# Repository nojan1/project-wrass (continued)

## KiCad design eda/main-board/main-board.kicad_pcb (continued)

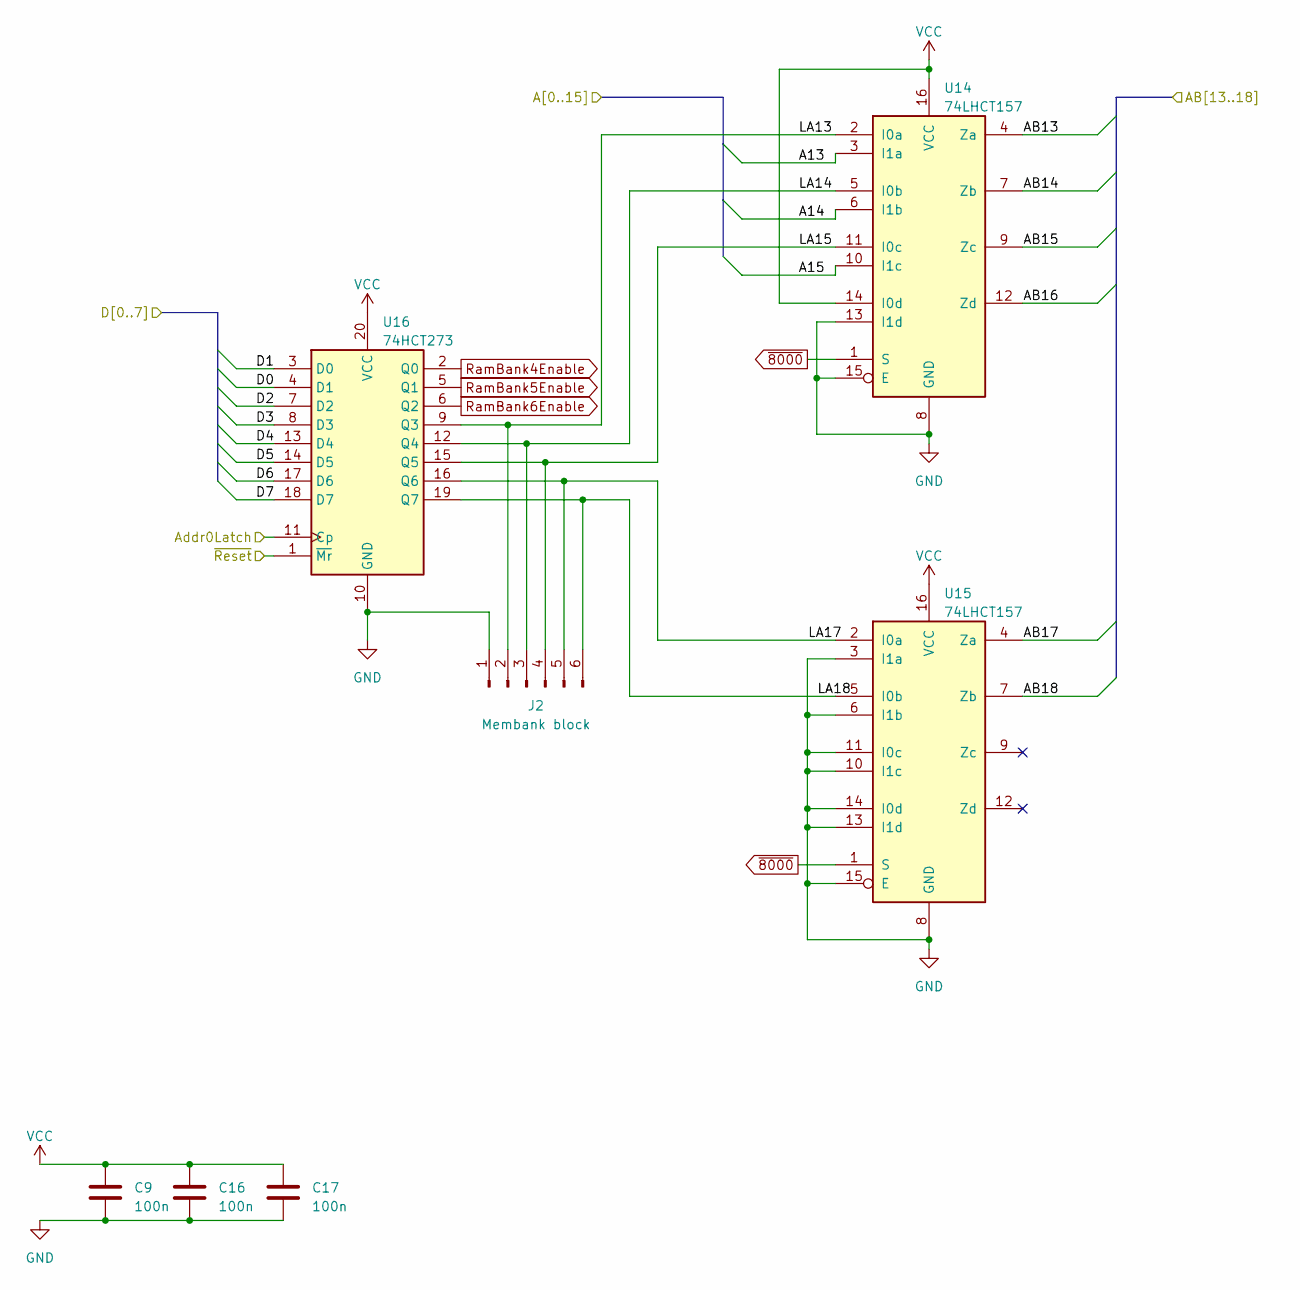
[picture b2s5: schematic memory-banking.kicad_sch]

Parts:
C9, C16, C17: 100n; C_Disc_D3.8mm_W2.6mm_P2.50mm
J2: Membank block; PinHeader_1x06_P2.54mm_Vertical
U14, U15: 74LHCT157; DIP-16_W7.62mm
U16: 74HCT273; DIP-20_W7.62mm

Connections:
/A13: U14.3 (I1a); also elsewhere on the board
/A14: U14.6 (I1b); also elsewhere on the board
/A15: U14.10 (I1c); also elsewhere on the board
/Address decode/Addr0Latch: U16.11 (Cp); also elsewhere on the board
/D0: U16.4 (D1); also elsewhere on the board
/D1: U16.3 (D0); also elsewhere on the board
/D2: U16.7 (D2); also elsewhere on the board
/D3: U16.8 (D3); also elsewhere on the board
/D4: U16.13 (D4); also elsewhere on the board
/D5: U16.14 (D5); also elsewhere on the board
/D6: U16.17 (D6); also elsewhere on the board
/D7: U16.18 (D7); also elsewhere on the board
/Expansion/~RST: U16.1 (~Mr); also elsewhere on the board
/Memory banking/AB13: U14.4 (Za); also elsewhere on the board
/Memory banking/AB14: U14.7 (Zb); also elsewhere on the board
/Memory banking/AB15: U14.9 (Zc); also elsewhere on the board
/Memory banking/AB16: U14.12 (Zd); also elsewhere on the board
/Memory banking/AB17: U15.4 (Za); also elsewhere on the board
/Memory banking/AB18: U15.7 (Zb); also elsewhere on the board
/Memory banking/LA13: J2.2, U14.2 (I0a), U16.9 (Q3)
/Memory banking/LA14: J2.3, U14.5 (I0b), U16.12 (Q4)
/Memory banking/LA15: J2.4, U14.11 (I0c), U16.15 (Q5)
/Memory banking/LA17: J2.5, U15.2 (I0a), U16.16 (Q6)
/Memory banking/LA18: J2.6, U15.5 (I0b), U16.19 (Q7)
GND: C9.2, C16.2, C17.2, J2.1, U14.8 (GND), U14.13 (I1d), U14.15 (E), U15.3 (I1a), U15.6 (I1b), U15.8 (GND), U15.10 (I1c), U15.11 (I0c), U15.13 (I1d), U15.14 (I0d), U15.15 (E), U16.10 (GND); also elsewhere on the board
RamBank4Enable: U16.2 (Q0); also elsewhere on the board
RamBank5Enable: U16.5 (Q1); also elsewhere on the board
RamBank6Enable: U16.6 (Q2); also elsewhere on the board
VCC: C9.1, C16.1, C17.1, U14.14 (I0d), U14.16 (VCC), U15.16 (VCC), U16.20 (VCC); also elsewhere on the board
~8000: U14.1 (S), U15.1 (S); also elsewhere on the board

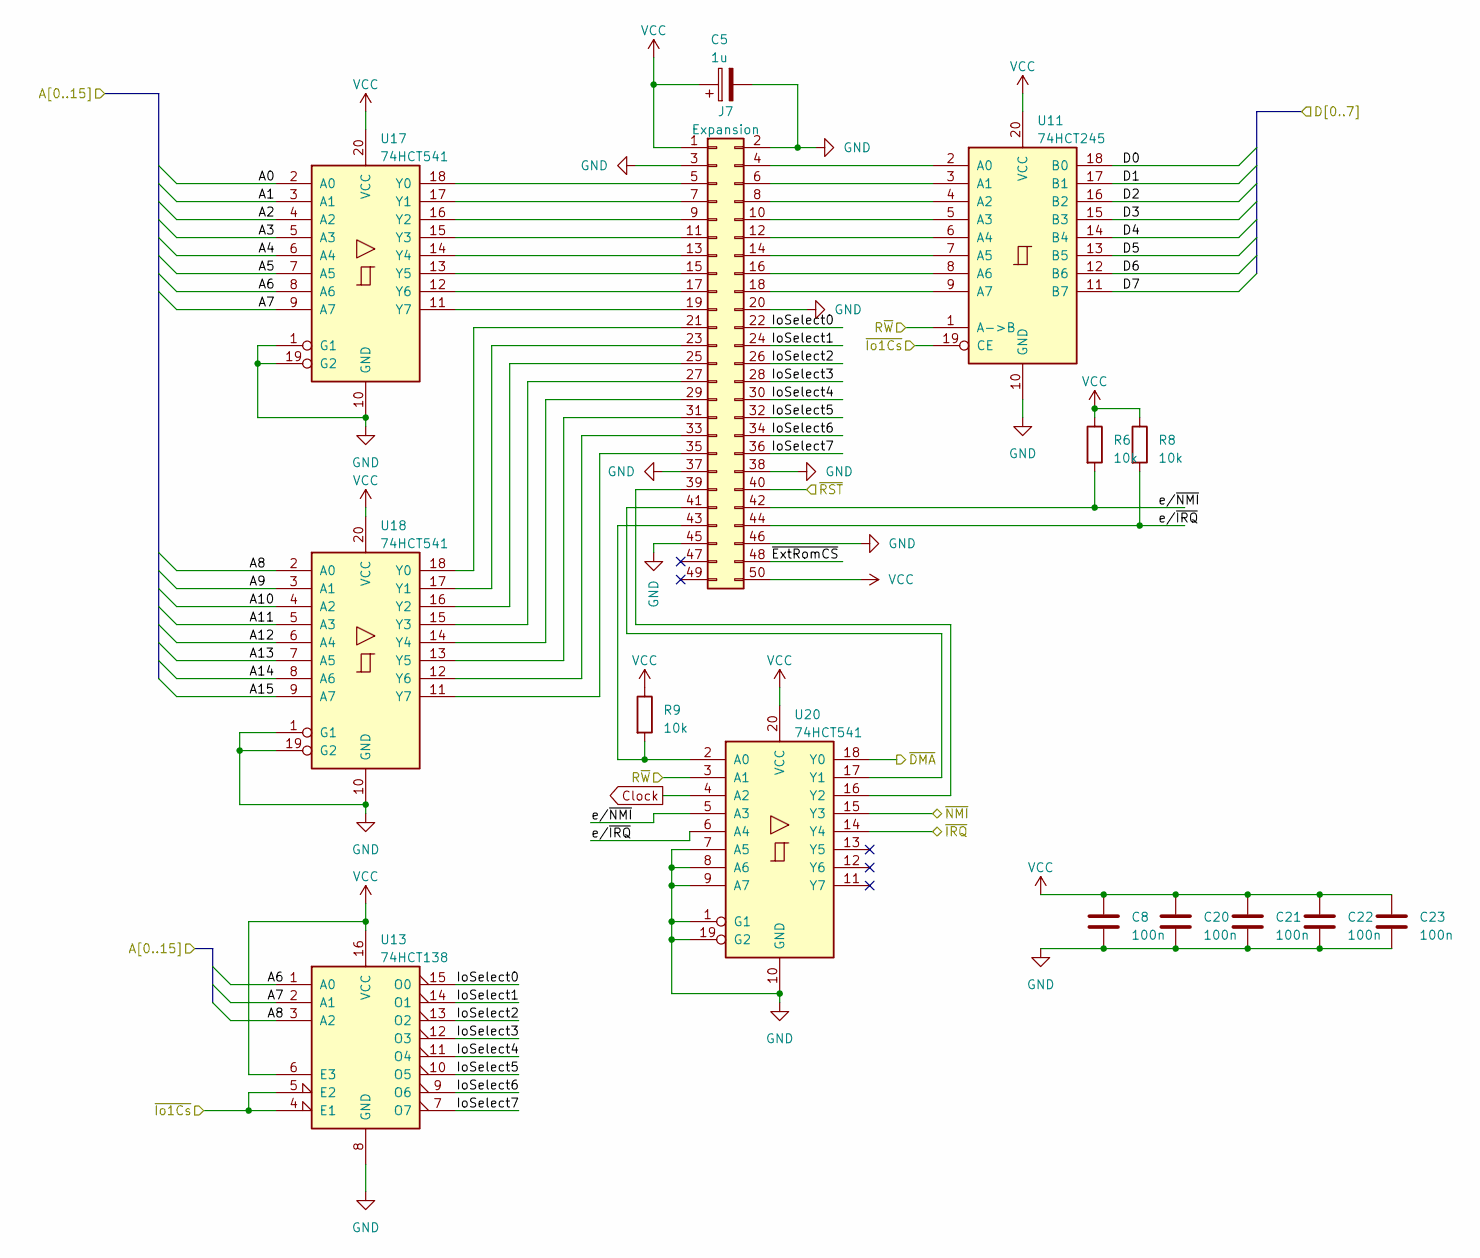
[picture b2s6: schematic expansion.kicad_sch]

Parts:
C5: 1u; CP_Radial_D8.0mm_P3.50mm
C8, C20, C21, C22, C23: 100n; C_Disc_D3.8mm_W2.6mm_P2.50mm
J7: Expansion; PinHeader_2x25_P2.54mm_Vertical
R6, R8, R9: 10k; R_Axial_DIN0207_L6.3mm_D2.5mm_P7.62mm_Horizontal
U11: 74HCT245; DIP-20_W7.62mm
U13: 74HCT138; DIP-16_W7.62mm
U17, U18, U20: 74HCT541; DIP-20_W7.62mm

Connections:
/A0: U17.2 (A0); also elsewhere on the board
/A1: U17.3 (A1); also elsewhere on the board
/A2: U17.4 (A2); also elsewhere on the board
/A3: U17.5 (A3); also elsewhere on the board
/A4: U17.6 (A4); also elsewhere on the board
/A5: U17.7 (A5); also elsewhere on the board
/A6: U13.1 (A0), U17.8 (A6); also elsewhere on the board
/A7: U13.2 (A1), U17.9 (A7); also elsewhere on the board
/A8: U13.3 (A2), U18.2 (A0); also elsewhere on the board
/A9: U18.3 (A1); also elsewhere on the board
/A10: U18.4 (A2); also elsewhere on the board
/A11: U18.5 (A3); also elsewhere on the board
/A12: U18.6 (A4); also elsewhere on the board
/A13: U18.7 (A5); also elsewhere on the board
/A14: U18.8 (A6); also elsewhere on the board
/A15: U18.9 (A7); also elsewhere on the board
/Address decode/R~W: U11.1 (A->B), U20.3 (A1); also elsewhere on the board
/Address decode/~Io1Cs: U11.19 (CE), U13.4 (E1), U13.5 (E2); also elsewhere on the board
/D0: U11.18 (B0); also elsewhere on the board
/D1: U11.17 (B1); also elsewhere on the board
/D2: U11.16 (B2); also elsewhere on the board
/D3: U11.15 (B3); also elsewhere on the board
/D4: U11.14 (B4); also elsewhere on the board
/D5: U11.13 (B5); also elsewhere on the board
/D6: U11.12 (B6); also elsewhere on the board
/D7: U11.11 (B7); also elsewhere on the board
/Expansion/IoSelect0: J7.22, U13.15 (O0)
/Expansion/IoSelect1: J7.24, U13.14 (O1)
/Expansion/IoSelect2: J7.26, U13.13 (O2)
/Expansion/IoSelect3: J7.28, U13.12 (O3)
/Expansion/IoSelect4: J7.30, U13.11 (O4)
/Expansion/IoSelect5: J7.32, U13.10 (O5)
/Expansion/IoSelect6: J7.34, U13.9 (O6)
/Expansion/IoSelect7: J7.36, U13.7 (O7)
/Expansion/e/~IRQ: J7.44, R8.2, U20.6 (A4)
/Expansion/e/~NMI: J7.42, R6.2, U20.5 (A3)
/Expansion/~DMA: U20.18 (Y0); also elsewhere on the board
/Expansion/~ExtRomCS: J7.48
/Expansion/~IRQ: U20.14 (Y4); also elsewhere on the board
/Expansion/~NMI: U20.15 (Y3); also elsewhere on the board
/Expansion/~RST: J7.40; also elsewhere on the board
Clock: U20.4 (A2); also elsewhere on the board
GND: C5.2, C8.2, C20.2, C21.2, C22.2, C23.2, J7.2, J7.3, J7.20, J7.37, J7.38, J7.45, J7.46, U11.10 (GND), U13.8 (GND), U17.1 (G1), U17.10 (GND), U17.19 (G2), U18.1 (G1), U18.10 (GND), U18.19 (G2), U20.1 (G1), U20.7 (A5), U20.8 (A6), U20.9 (A7), U20.10 (GND), U20.19 (G2); also elsewhere on the board
unnamed: J7.4, U11.2 (A0)
unnamed: J7.5, U17.18 (Y0)
unnamed: J7.6, U11.3 (A1)
unnamed: J7.7, U17.17 (Y1)
unnamed: J7.8, U11.4 (A2)
unnamed: J7.9, U17.16 (Y2)
unnamed: J7.10, U11.5 (A3)
unnamed: J7.11, U17.15 (Y3)
unnamed: J7.12, U11.6 (A4)
unnamed: J7.13, U17.14 (Y4)
unnamed: J7.14, U11.7 (A5)
unnamed: J7.15, U17.13 (Y5)
unnamed: J7.16, U11.8 (A6)
unnamed: J7.17, U17.12 (Y6)
unnamed: J7.18, U11.9 (A7)
unnamed: J7.19, U17.11 (Y7)
unnamed: J7.21, U18.18 (Y0)
unnamed: J7.23, U18.17 (Y1)
unnamed: J7.25, U18.16 (Y2)
unnamed: J7.27, U18.15 (Y3)
unnamed: J7.29, U18.14 (Y4)
unnamed: J7.31, U18.13 (Y5)
unnamed: J7.33, U18.12 (Y6)
unnamed: J7.35, U18.11 (Y7)
unnamed: J7.39, U20.16 (Y2)
unnamed: J7.41, U20.17 (Y1)
unnamed: J7.43, R9.2, U20.2 (A0)
VCC: C5.1, C8.1, C20.1, C21.1, C22.1, C23.1, J7.1, J7.50, R6.1, R8.1, R9.1, U11.20 (VCC), U13.6 (E3), U13.16 (VCC), U17.20 (VCC), U18.20 (VCC), U20.20 (VCC); also elsewhere on the board

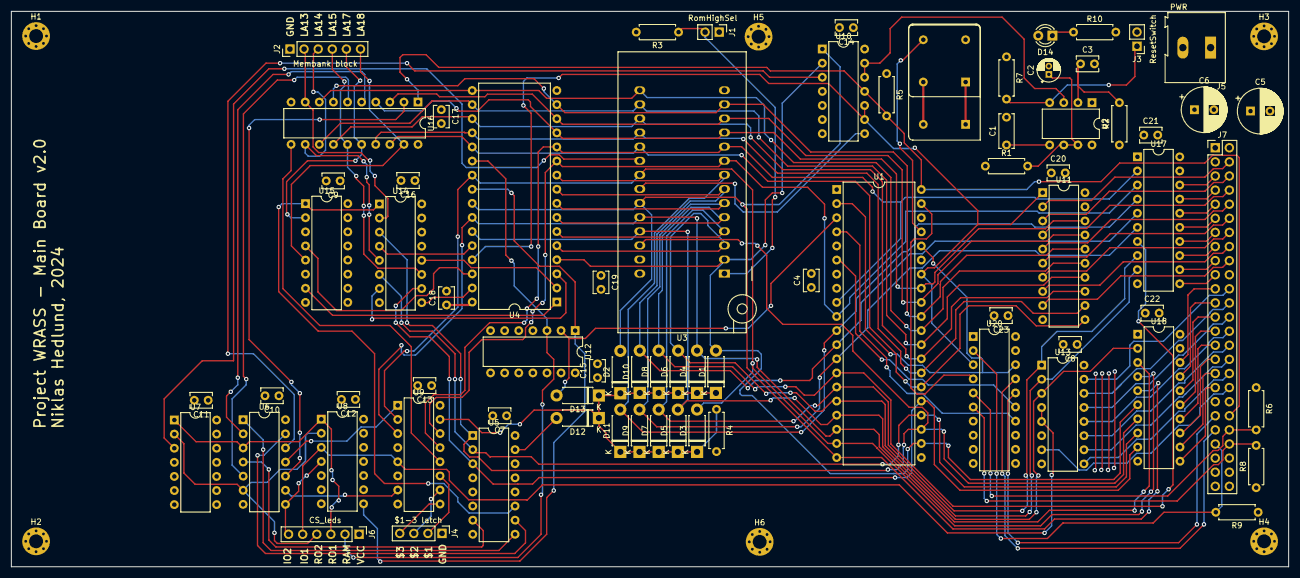
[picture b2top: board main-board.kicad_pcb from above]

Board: 4 copper layers, 230.0 x 100.0 mm, 80 parts (0 on the bottom side), 113 nets.

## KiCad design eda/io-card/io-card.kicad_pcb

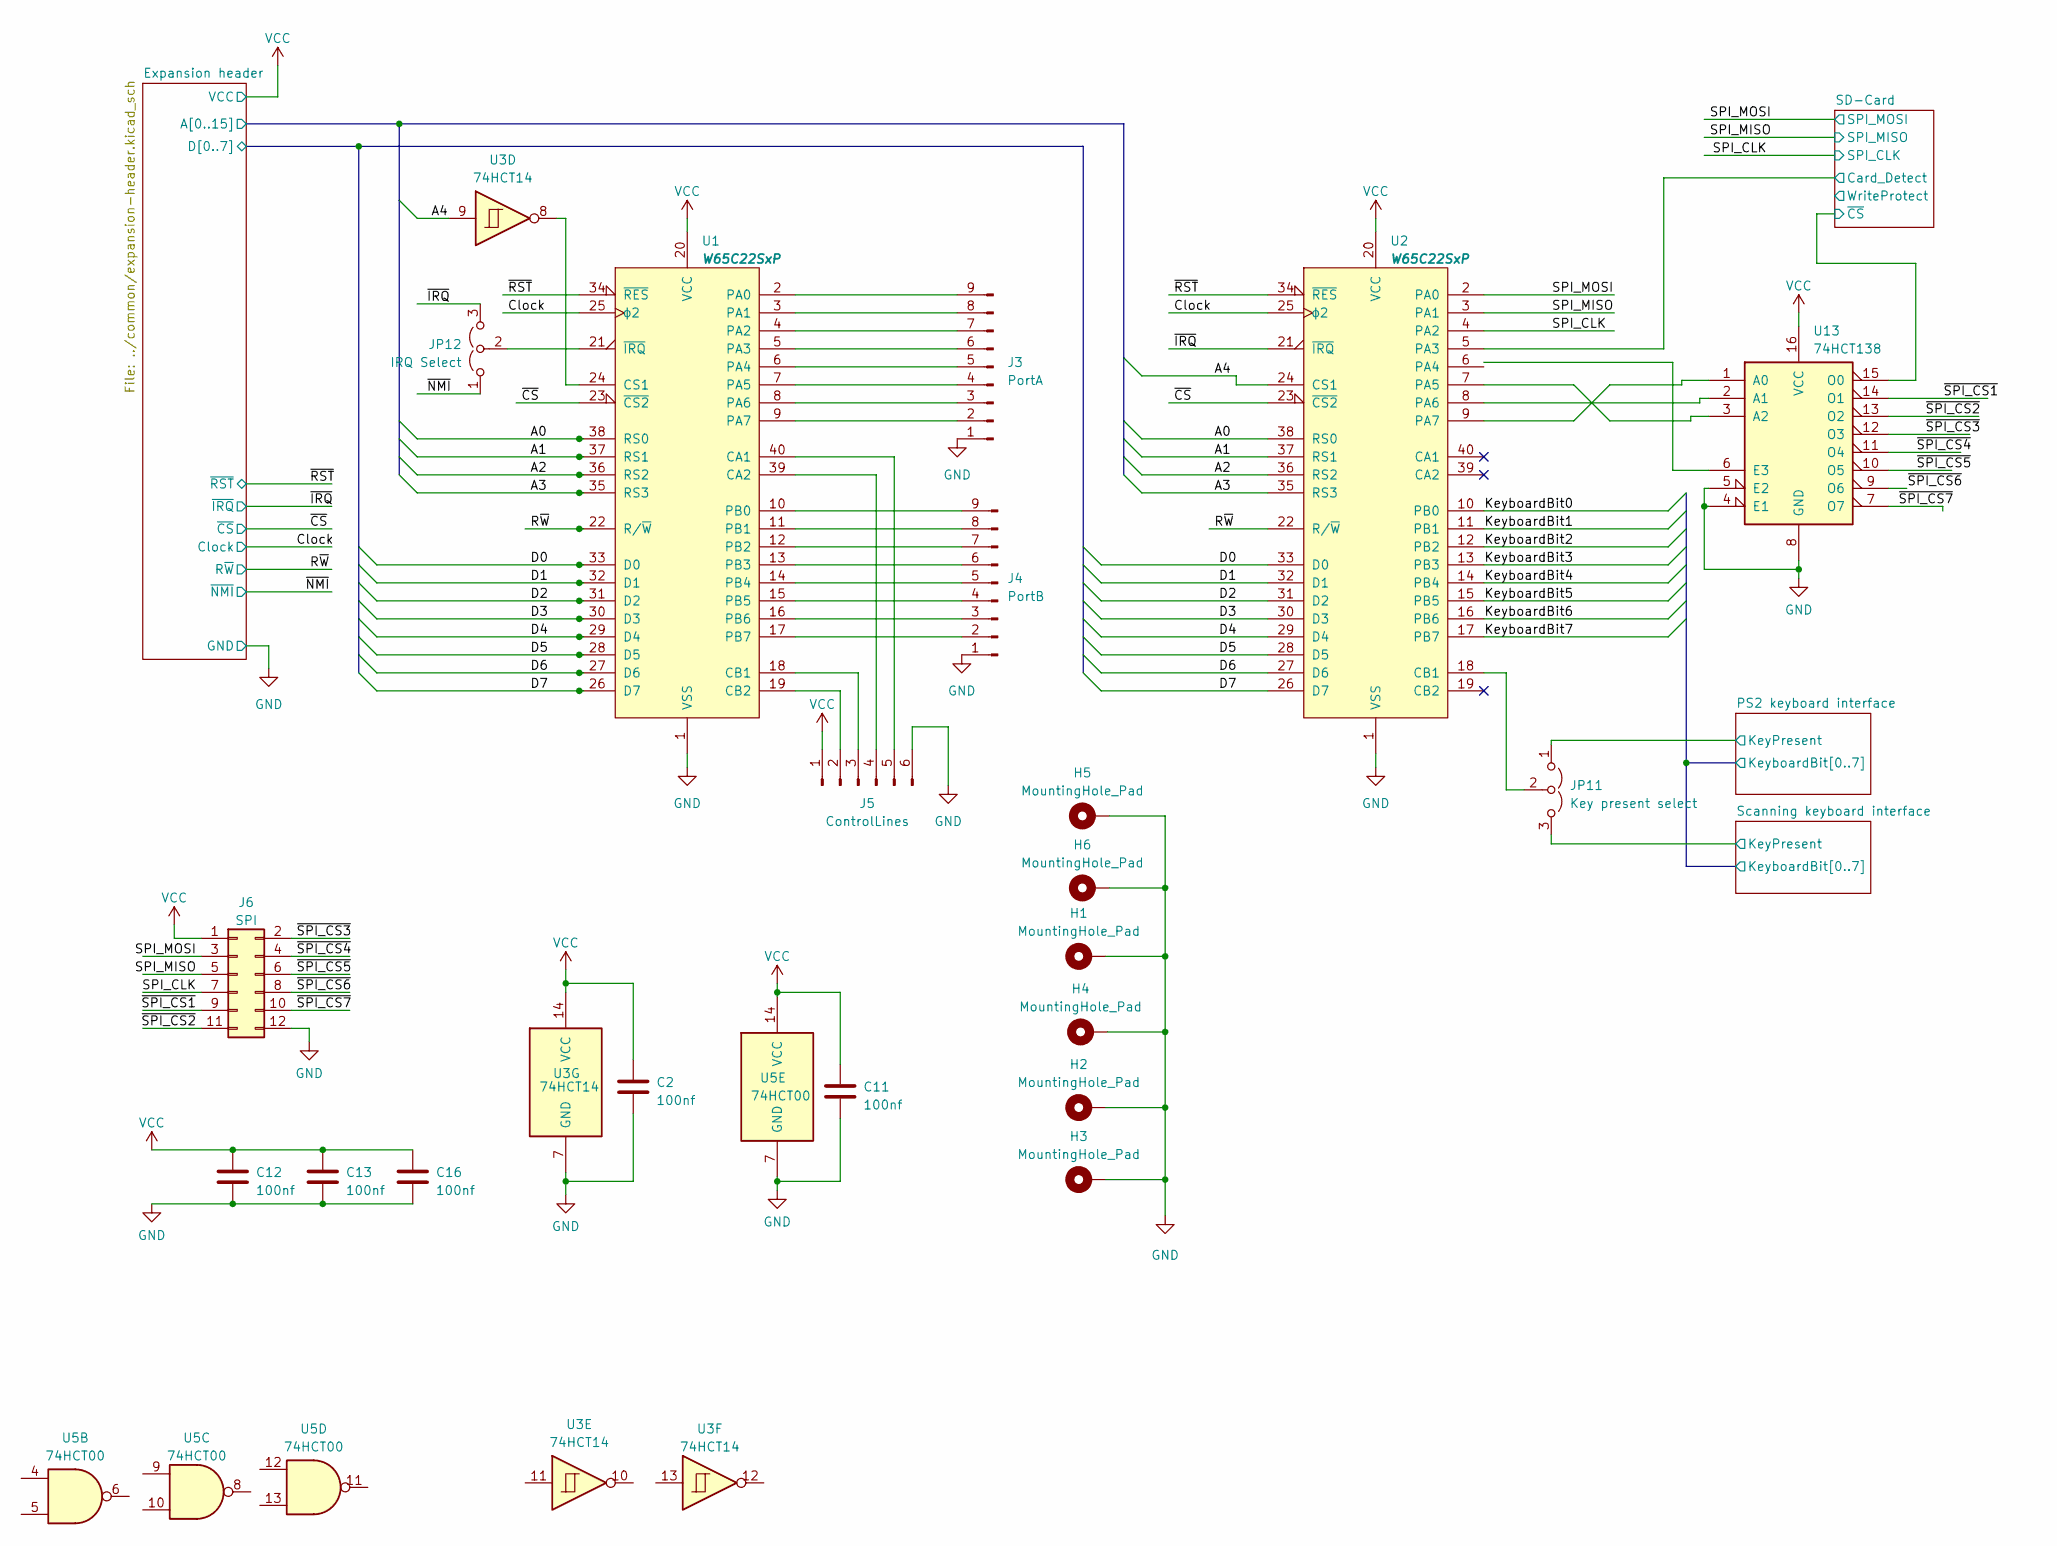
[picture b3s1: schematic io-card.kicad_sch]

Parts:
C2, C11, C12, C13, C16: 100nf; C_Disc_D3.8mm_W2.6mm_P2.50mm
H1, H2, H3, H4, H5, H6: MountingHole_Pad; MountingHole_2.5mm_Pad_Via
J3: PortA; PinHeader_1x09_P2.54mm_Horizontal
J4: PortB; PinHeader_1x09_P2.54mm_Horizontal
J5: ControlLines; PinHeader_1x06_P2.54mm_Horizontal
J6: SPI; PinHeader_2x06_P2.54mm_Horizontal
JP11: Key present select; PinHeader_1x03_P2.54mm_Vertical
JP12: IRQ Select; PinHeader_1x03_P2.54mm_Vertical
U1, U2: W65C22SxP; DIP-40_W15.24mm
U3: 74HCT14; DIP-14_W7.62mm
U5: 74HCT00; DIP-14_W7.62mm
U13: 74HCT138; DIP-16_W7.62mm

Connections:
/Card_Detect: U2.5 (PA3)
/Clock: U1.25 (ϕ2), U2.25 (ϕ2); also elsewhere on the board
/Expansion header/A0: U1.38 (RS0), U2.38 (RS0); also elsewhere on the board
/Expansion header/A1: U1.37 (RS1), U2.37 (RS1); also elsewhere on the board
/Expansion header/A2: U1.36 (RS2), U2.36 (RS2); also elsewhere on the board
/Expansion header/A3: U1.35 (RS3), U2.35 (RS3); also elsewhere on the board
/Expansion header/A4: U2.24 (CS1), U3.9; also elsewhere on the board
/Expansion header/D0: U1.33 (D0), U2.33 (D0); also elsewhere on the board
/Expansion header/D1: U1.32 (D1), U2.32 (D1); also elsewhere on the board
/Expansion header/D2: U1.31 (D2), U2.31 (D2); also elsewhere on the board
/Expansion header/D3: U1.30 (D3), U2.30 (D3); also elsewhere on the board
/Expansion header/D4: U1.29 (D4), U2.29 (D4); also elsewhere on the board
/Expansion header/D5: U1.28 (D5), U2.28 (D5); also elsewhere on the board
/Expansion header/D6: U1.27 (D6), U2.27 (D6); also elsewhere on the board
/Expansion header/D7: U1.26 (D7), U2.26 (D7); also elsewhere on the board
/PS2 keyboard interface/KeyPresent: JP11.1 (A); also elsewhere on the board
/PS2 keyboard interface/KeyboardBit0: U2.10 (PB0); also elsewhere on the board
/PS2 keyboard interface/KeyboardBit1: U2.11 (PB1); also elsewhere on the board
/PS2 keyboard interface/KeyboardBit2: U2.12 (PB2); also elsewhere on the board
/PS2 keyboard interface/KeyboardBit3: U2.13 (PB3); also elsewhere on the board
/PS2 keyboard interface/KeyboardBit4: U2.14 (PB4); also elsewhere on the board
/PS2 keyboard interface/KeyboardBit5: U2.15 (PB5); also elsewhere on the board
/PS2 keyboard interface/KeyboardBit6: U2.16 (PB6); also elsewhere on the board
/PS2 keyboard interface/KeyboardBit7: U2.17 (PB7); also elsewhere on the board
/R~W: U1.22 (R/~W), U2.22 (R/~W); also elsewhere on the board
/SD-Card/WriteProtect: U2.6 (PA4); also elsewhere on the board
/SD-Card/~CS: U13.15 (O0); also elsewhere on the board
/SPI_CLK: J6.7, U2.4 (PA2); also elsewhere on the board
/SPI_MISO: J6.5, U2.3 (PA1); also elsewhere on the board
/SPI_MOSI: J6.3, U2.2 (PA0); also elsewhere on the board
/Scanning keyboard interface/KeyPresent: JP11.3 (B); also elsewhere on the board
/~CS: U1.23 (~CS2), U2.23 (~CS2); also elsewhere on the board
/~IRQ: JP12.3 (B), U2.21 (~IRQ); also elsewhere on the board
/~NMI: JP12.1 (A); also elsewhere on the board
/~RST: U1.34 (~RES), U2.34 (~RES); also elsewhere on the board
/~SPI_CS1: J6.9, U13.14 (O1)
/~SPI_CS2: J6.11, U13.13 (O2)
/~SPI_CS3: J6.2, U13.12 (O3)
/~SPI_CS4: J6.4, U13.11 (O4)
/~SPI_CS5: J6.6, U13.10 (O5)
/~SPI_CS6: J6.8, U13.9 (O6)
/~SPI_CS7: J6.10, U13.7 (O7)
GND: C2.2, C11.2, C12.2, C13.2, C16.2, H1.1, H2.1, H3.1, H4.1, H5.1, H6.1, J3.1, J4.1, J5.6, J6.12, U1.1 (VSS), U2.1 (VSS), U3.7 (GND), U5.7 (GND), U13.4 (E1), U13.5 (E2), U13.8 (GND); also elsewhere on the board
unnamed: J3.2, U1.9 (PA7)
unnamed: J3.3, U1.8 (PA6)
unnamed: J3.4, U1.7 (PA5)
unnamed: J3.5, U1.6 (PA4)
unnamed: J3.6, U1.5 (PA3)
unnamed: J3.7, U1.4 (PA2)
unnamed: J3.8, U1.3 (PA1)
unnamed: J3.9, U1.2 (PA0)
unnamed: J4.2, U1.17 (PB7)
unnamed: J4.3, U1.16 (PB6)
unnamed: J4.4, U1.15 (PB5)
unnamed: J4.5, U1.14 (PB4)
unnamed: J4.6, U1.13 (PB3)
unnamed: J4.7, U1.12 (PB2)
unnamed: J4.8, U1.11 (PB1)
unnamed: J4.9, U1.10 (PB0)
unnamed: J5.2, U1.19 (CB2)
unnamed: J5.3, U1.18 (CB1)
unnamed: J5.4, U1.39 (CA2)
unnamed: J5.5, U1.40 (CA1)
unnamed: JP11.2 (C), U2.18 (CB1)
unnamed: JP12.2 (C), U1.21 (~IRQ)
unnamed: U1.24 (CS1), U3.8
unnamed: U2.9 (PA7), U13.1 (A0)
unnamed: U2.8 (PA6), U13.2 (A1)
unnamed: U2.7 (PA5), U13.3 (A2)
VCC: C2.1, C11.1, C12.1, C13.1, C16.1, J5.1, J6.1, U1.20 (VCC), U2.20 (VCC), U3.14 (VCC), U5.14 (VCC), U13.6 (E3), U13.16 (VCC); also elsewhere on the board

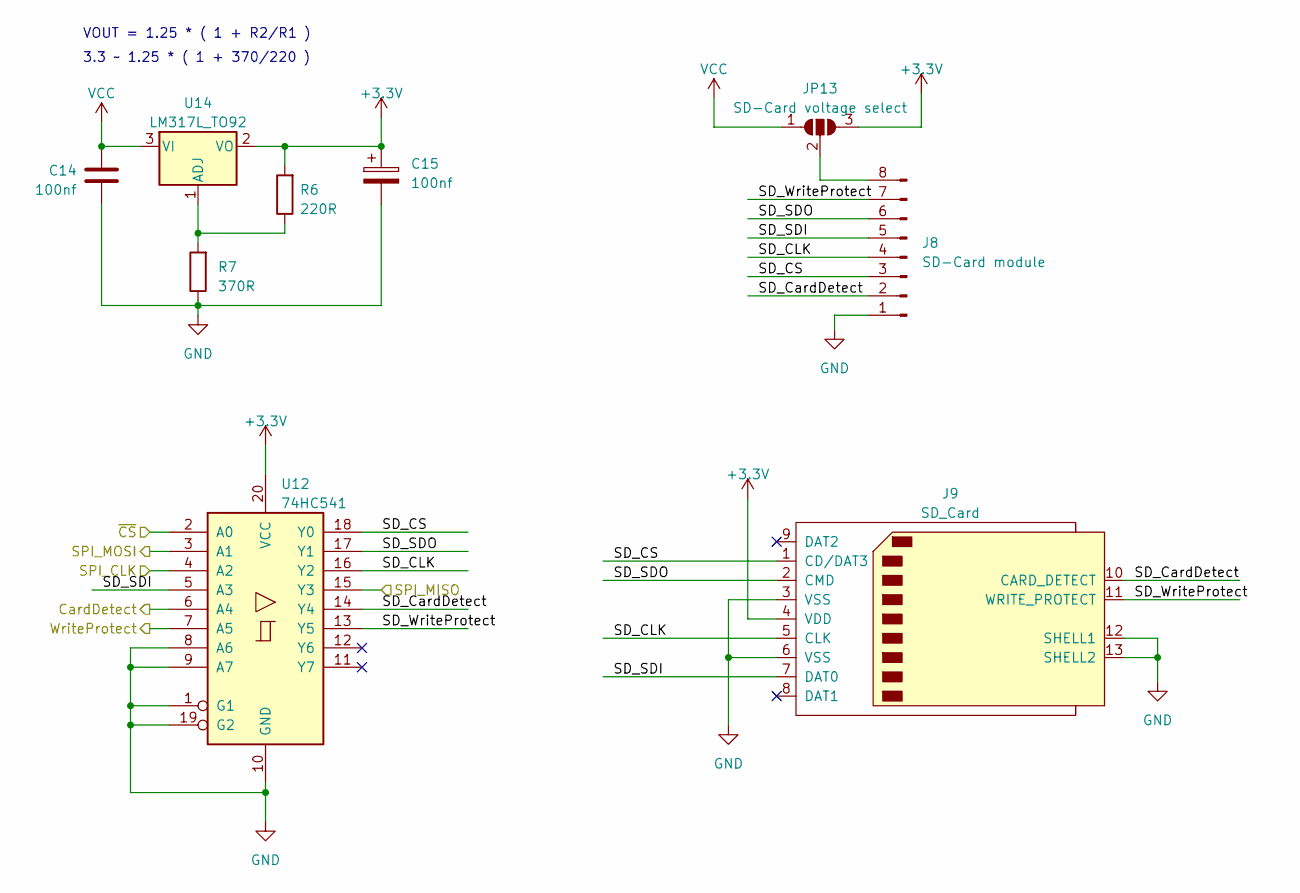
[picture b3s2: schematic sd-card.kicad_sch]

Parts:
C14: 100nf; C_Disc_D3.8mm_W2.6mm_P2.50mm
C15: 100nf; C_Radial_D4.0mm_H5.0mm_P1.50mm
J8: SD-Card module; PinHeader_1x08_P2.54mm_Vertical
J9: SD_Card; SD_Kyocera_145638109511859+
JP13: SD-Card voltage select; SolderJumper-3_P1.3mm_Open_Pad1.0x1.5mm
R6: 220R; R_Axial_DIN0204_L3.6mm_D1.6mm_P5.08mm_Horizontal
R7: 370R; R_Axial_DIN0204_L3.6mm_D1.6mm_P5.08mm_Horizontal
U12: 74HC541; DIP-20_W7.62mm
U14: LM317L_TO92; TO-92_Inline

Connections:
+3.3V: C15.1, J9.4 (VDD), JP13.3 (B), R6.2, U12.20 (VCC), U14.2 (VO)
/SD-Card/CardDetect: U12.6 (A4)
/SD-Card/SD_CLK: J8.4, J9.5 (CLK), U12.16 (Y2)
/SD-Card/SD_CS: J8.3, J9.1 (CD/DAT3), U12.18 (Y0)
/SD-Card/SD_CardDetect: J8.2, J9.10 (CARD_DETECT), U12.14 (Y4)
/SD-Card/SD_SDI: J8.5, J9.7 (DAT0), U12.5 (A3)
/SD-Card/SD_SDO: J8.6, J9.2 (CMD), U12.17 (Y1)
/SD-Card/SD_WriteProtect: J8.7, J9.11 (WRITE_PROTECT), U12.13 (Y5)
/SD-Card/WriteProtect: U12.7 (A5); also elsewhere on the board
/SD-Card/~CS: U12.2 (A0); also elsewhere on the board
/SPI_CLK: U12.4 (A2); also elsewhere on the board
/SPI_MISO: U12.15 (Y3); also elsewhere on the board
/SPI_MOSI: U12.3 (A1); also elsewhere on the board
GND: C14.2, C15.2, J8.1, J9.3 (VSS), J9.6 (VSS), J9.12 (SHELL1), J9.13 (SHELL2), R7.1, U12.1 (G1), U12.8 (A6), U12.9 (A7), U12.10 (GND), U12.19 (G2); also elsewhere on the board
unnamed: J8.8, JP13.2 (C)
unnamed: R6.1, R7.2, U14.1 (ADJ)
VCC: C14.1, JP13.1 (A), U14.3 (VI); also elsewhere on the board

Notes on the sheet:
VOUT = 1.25 * ( 1 + R2/R1 )
3.3 ~ 1.25 * ( 1 + 370/220 )

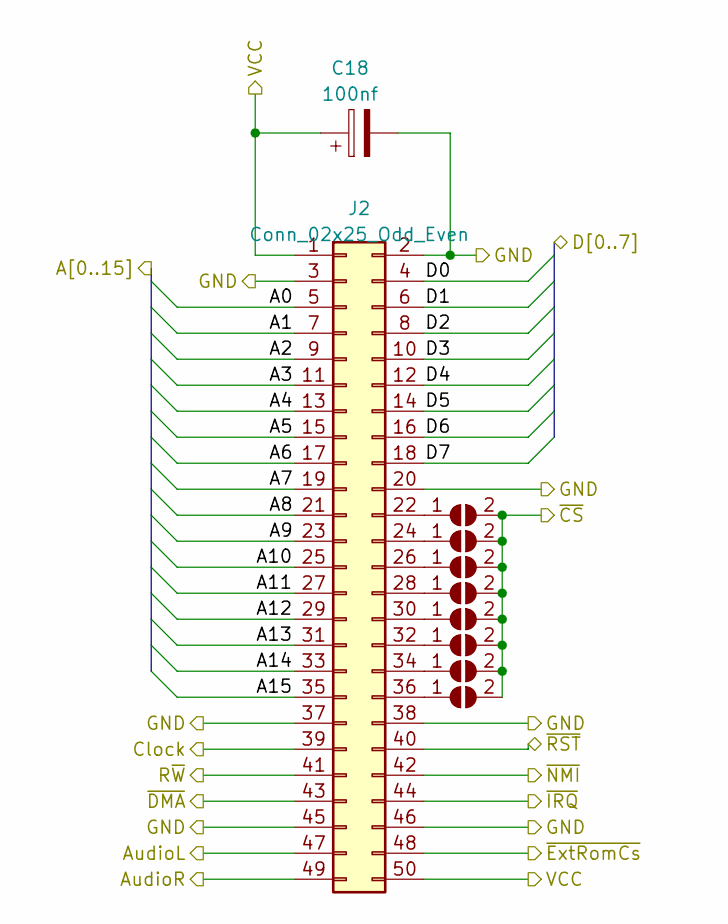
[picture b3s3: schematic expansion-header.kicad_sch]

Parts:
C18: 100nf; C_Radial_D5.0mm_H7.0mm_P2.00mm
J2: Conn_02x25_Odd_Even; PinHeader_2x25_P2.54mm_Vertical
JP1, JP2, JP3, JP4, JP5, JP6, JP7, JP8: SolderJumper_2_Open; SolderJumper-2_P1.3mm_Open_RoundedPad1.0x1.5mm

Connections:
/Clock: J2.39; also elsewhere on the board
/Expansion header/A0: J2.5; also elsewhere on the board
/Expansion header/A1: J2.7; also elsewhere on the board
/Expansion header/A2: J2.9; also elsewhere on the board
/Expansion header/A3: J2.11; also elsewhere on the board
/Expansion header/A4: J2.13; also elsewhere on the board
/Expansion header/A5: J2.15
/Expansion header/A6: J2.17
/Expansion header/A7: J2.19
/Expansion header/A8: J2.21
/Expansion header/A9: J2.23
/Expansion header/A10: J2.25
/Expansion header/A11: J2.27
/Expansion header/A12: J2.29
/Expansion header/A13: J2.31
/Expansion header/A14: J2.33
/Expansion header/A15: J2.35
/Expansion header/AudioL: J2.47
/Expansion header/AudioR: J2.49
/Expansion header/D0: J2.4; also elsewhere on the board
/Expansion header/D1: J2.6; also elsewhere on the board
/Expansion header/D2: J2.8; also elsewhere on the board
/Expansion header/D3: J2.10; also elsewhere on the board
/Expansion header/D4: J2.12; also elsewhere on the board
/Expansion header/D5: J2.14; also elsewhere on the board
/Expansion header/D6: J2.16; also elsewhere on the board
/Expansion header/D7: J2.18; also elsewhere on the board
/Expansion header/~DMA: J2.43
/Expansion header/~ExtRomCs: J2.48
/R~W: J2.41; also elsewhere on the board
/~CS: JP1.2 (B), JP2.2 (B), JP3.2 (B), JP4.2 (B), JP5.2 (B), JP6.2 (B), JP7.2 (B), JP8.2 (B); also elsewhere on the board
/~IRQ: J2.44; also elsewhere on the board
/~NMI: J2.42; also elsewhere on the board
/~RST: J2.40; also elsewhere on the board
GND: C18.2, J2.2, J2.3, J2.20, J2.37, J2.38, J2.45, J2.46; also elsewhere on the board
unnamed: J2.22, JP1.1 (A)
unnamed: J2.24, JP2.1 (A)
unnamed: J2.26, JP3.1 (A)
unnamed: J2.28, JP4.1 (A)
unnamed: J2.30, JP5.1 (A)
unnamed: J2.32, JP6.1 (A)
unnamed: J2.34, JP7.1 (A)
unnamed: J2.36, JP8.1 (A)
VCC: C18.1, J2.1, J2.50; also elsewhere on the board

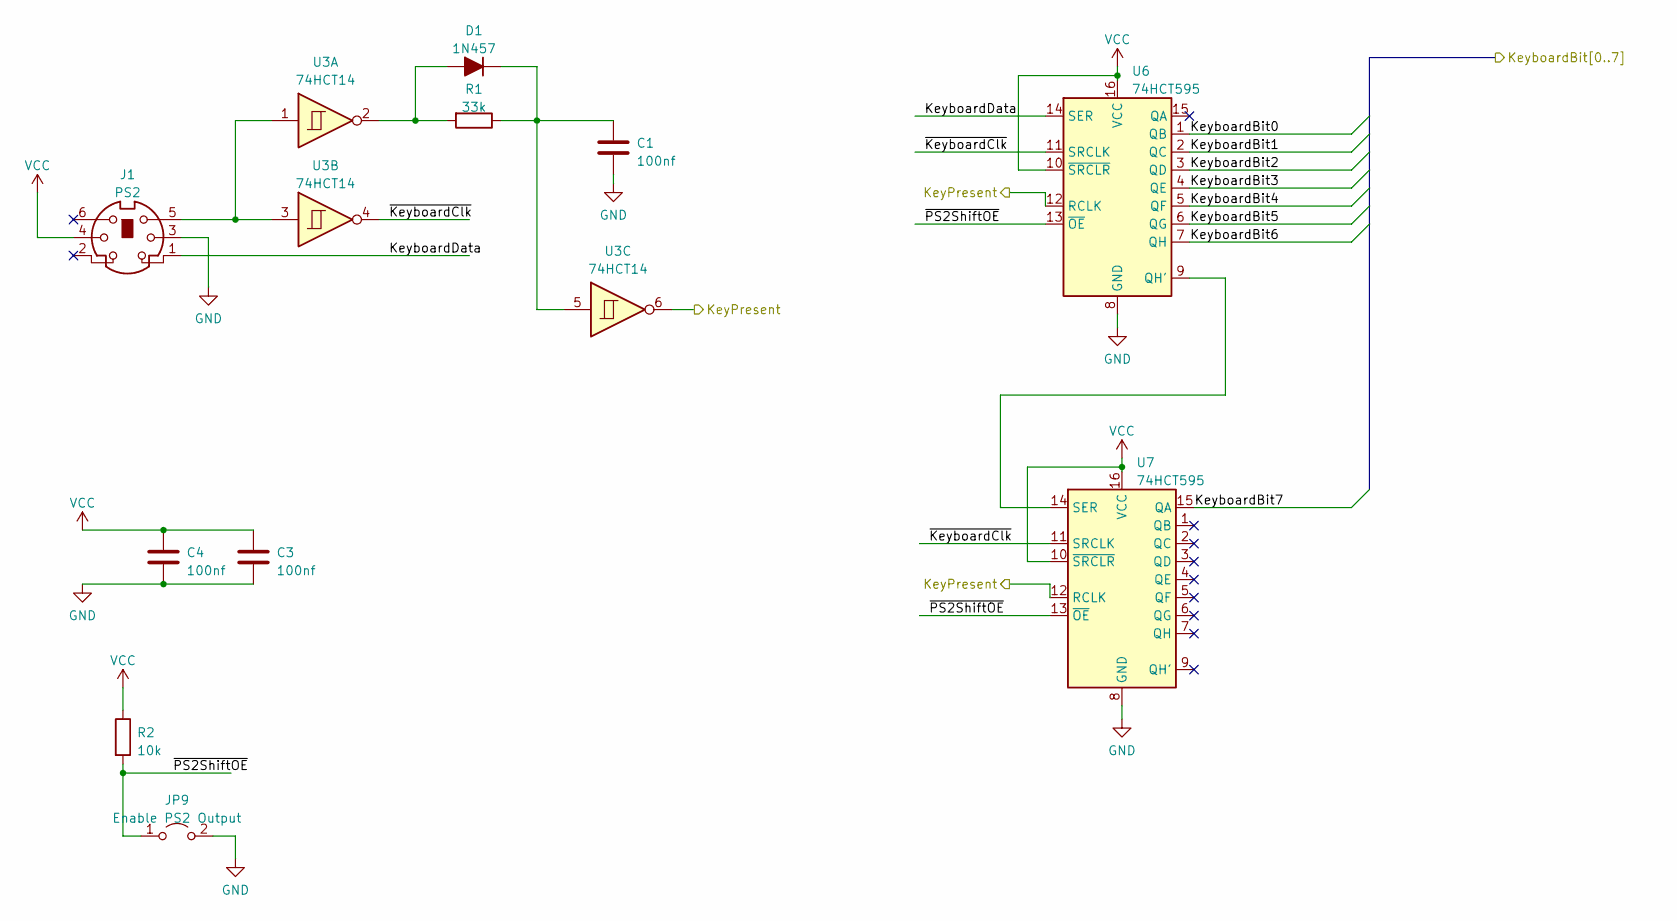
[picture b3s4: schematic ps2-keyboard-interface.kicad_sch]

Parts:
C1, C3, C4: 100nf; C_Disc_D3.8mm_W2.6mm_P2.50mm
D1: 1N457; D_DO-35_SOD27_P7.62mm_Horizontal
J1: PS2; Connector_Mini-DIN_Female_6Pin_2rows
JP9: Enable PS2 Output; PinHeader_1x02_P2.54mm_Vertical
R1: 33k; R_Axial_DIN0204_L3.6mm_D1.6mm_P5.08mm_Horizontal
R2: 10k; R_Axial_DIN0204_L3.6mm_D1.6mm_P5.08mm_Horizontal
U3: 74HCT14; DIP-14_W7.62mm
U6, U7: 74HCT595; DIP-16_W7.62mm

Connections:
/PS2 keyboard interface/KeyPresent: U3.6, U6.12 (RCLK), U7.12 (RCLK); also elsewhere on the board
/PS2 keyboard interface/KeyboardBit0: U6.1 (QB); also elsewhere on the board
/PS2 keyboard interface/KeyboardBit1: U6.2 (QC); also elsewhere on the board
/PS2 keyboard interface/KeyboardBit2: U6.3 (QD); also elsewhere on the board
/PS2 keyboard interface/KeyboardBit3: U6.4 (QE); also elsewhere on the board
/PS2 keyboard interface/KeyboardBit4: U6.5 (QF); also elsewhere on the board
/PS2 keyboard interface/KeyboardBit5: U6.6 (QG); also elsewhere on the board
/PS2 keyboard interface/KeyboardBit6: U6.7 (QH); also elsewhere on the board
/PS2 keyboard interface/KeyboardBit7: U7.15 (QA); also elsewhere on the board
/PS2 keyboard interface/KeyboardData: J1.1, U6.14 (SER)
/PS2 keyboard interface/~KeyboardClk: U3.4, U6.11 (SRCLK), U7.11 (SRCLK)
/PS2 keyboard interface/~PS2ShiftOE: JP9.1 (A), R2.2, U6.13 (~OE), U7.13 (~OE)
GND: C1.2, C3.2, C4.2, J1.3, JP9.2 (B), U6.8 (GND), U7.8 (GND); also elsewhere on the board
unnamed: D1.2 (A), R1.2, U3.2
unnamed: C1.1, D1.1 (K), R1.1, U3.5
unnamed: J1.5, U3.1, U3.3
unnamed: U6.9 (QH'), U7.14 (SER)
VCC: C3.1, C4.1, J1.4, R2.1, U6.10 (~SRCLR), U6.16 (VCC), U7.10 (~SRCLR), U7.16 (VCC); also elsewhere on the board

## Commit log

2021-10-25 Add clock sketch
2021-10-27 Added README
2021-10-31 Did work on simulator
2021-10-31 Added on_step callback to MPU
2021-10-31 Via responding to commands
2021-11-01 Add LCD drawing
2021-11-01 Updated font
2021-11-08 Simulator can run 'LCD'
2021-11-15 Add build tasks for vscode
2021-11-17 Add initial stub for the kernel
2021-11-17 rts => rti
2021-11-17 Add nop for good measure
2021-11-19 Add working Clock sketch
2021-11-23 Add the archtiecture file
2021-11-23 Refactor asm directory
2021-11-24 Add tile-editor
2021-12-01 Added bitmap mode to docs
2022-02-21 Update architecture
2022-03-03 Updated docs
2022-03-03 Initial work on bank switch
2022-03-06 New electron based simulator
2022-03-06 Initial file loading
2022-03-07 Refactoring
2022-03-07 Design fix
2022-03-07 Moved to use context for datapassing
2022-03-08 Blinkenlights working
2022-03-08 Lcd display working
2022-03-09 Parse listing file and use info
2022-03-09 Working vscode integration
2022-03-09 Decode keypresses to scancodes
2022-03-10 First steps to a working keyboard routine
2022-03-11 Memory explorer works
2022-03-15 Partial working string comparison
2022-03-16 Continued command parsing
2022-03-16 Add flags output to simulator
2022-03-19 Bigger lcd and working newline
2022-03-19 Operands thrown around in str_startswith
2022-04-02 Working 65c02 stuff
2022-04-03 Restructure rom layout into monitor / kernel areas
2022-04-03 Helper script to run experiments
2022-04-05 Fix bug in keyboard controller
2022-04-05 Hex encode for output
2022-04-05 Can trigger other commands
2022-04-06 Changed command jump logic
2022-04-07 Shrink the IO area
2022-04-07 Update steps done
2022-04-11 Add display of breakpoints and ability to turn them on and off
2022-04-11 Can convert single hex character to num
2022-04-11 Working hex parsing
2022-04-11 Don't send keyboard events if the debugger is not running
2022-04-11 Write command works
2022-04-12 Can render framebuffer
2022-04-13 Monitor kind of works with graphic output
2022-04-13 Graphic output working and restructure
2022-04-14 Working backspace
2022-04-17 Add initial support for SPI
2022-04-19 Spi communication seems to work
2022-04-20 Skeleton of SD card support in simulator
2022-04-21 SPI sd card communication interim commit
2022-04-21 Add auto rescale to canvas
2022-04-21 Can initialize sd card
2022-04-21 Fix is empty bug in shifter
2022-04-22 Can read sd card bytes but not correctly
2022-04-25 Somewhat stableich reading of SD card
2022-04-25 Can read partition type and partition start address from MBR
2022-05-03 Start on fat partition reading code
2022-05-04 Start creating some diagnostics code
2022-05-05 Bugfix input buffer collides with stack
2022-05-05 Test RAM(1)
2022-05-05 More tests
2022-05-31 Fix near far bug
2022-06-01 Add support for reading breakpoints in comments
2022-06-03 Add fake gpu implementation for arduino
2022-06-21 Work on debugging
2022-07-06 Added build script
2022-08-17 Changed out of range check for command
2022-09-02 Changed place of memory and IO in $A000
2022-10-09 Memory banking support in simulator and diag rom
2022-10-31 Add render
2022-11-01 Add color pallete visual
2022-11-07 Working scroll in simulator
2022-11-22 Somewhat working verilog (?) code
2022-11-30 More work on GPU rendering
2022-11-30 Reduced screen size due to available FPGA block mem
2022-12-15 Gpu refactor
2023-01-05 Refactored memory into seperate block instances
2023-01-05 Add bus interface module
2023-01-09 Add js output support to export window
2023-01-09 Improve import code
2023-01-09 Add script to generate character set
2023-01-10 Emulator support screencode
2023-01-10 Verilog code now uses new tileset
2023-01-13 Reset pixel generator during vga blank
2023-01-13 Add new banner
2023-01-18 Use count from clock divider in pixel generator
2023-01-21 Blue line is only 2 bits
2023-01-21 Can't read from GPU atm
2023-02-02 Invert clock triggering to get in sync with VGA monitor
2023-02-05 Initialize video memory on display_init
2023-02-07 Do blocking assignment to block ram for bus interface
2023-02-23 Use FPGA clock for memory writes, buffer CPU writes in register
2023-03-28 Math and gpu work
2023-03-28 Add eda folder for kicad
2023-03-28 Add first draft for uart
2023-03-29 More work on UART
2023-03-31 Port main board schematic to kicad
2023-04-07 Work on main board eda, interim
2023-04-07 GPU routing
2023-04-09 More routing on the GPU board
2023-05-06 Update eda
2023-05-07 Convert expansion breakout to kicad
2023-05-07 Add skeleton stuff to io-card and gpu
2023-05-12 Add expansion backplane
2023-05-16 Add audio card
2023-05-23 Change pinout to not use expansion board
2023-07-07 Interim commit
2023-07-07 Trigger memory write from falling cpu clock
2023-07-07 Text output subsystem now supports multiple active devices
2023-07-07 Update location of UART
2023-07-08 Incorrect stack operation, replace with transfer
2023-07-08 Update cap footprint
2023-07-15 Update diagnostic to support new output subsystem
2023-07-15 Add missing file
2023-07-15 Started work on testrunner
2023-07-16 Test runner seems to run something
2023-07-20 Update UART transmit logic
2023-07-20 Prelimary UART routing
2023-07-20 Fix bug when check IOCONTROL
2023-07-22 Start converting audio card to analog synth base
2024-01-02 Sync
2024-01-07 EDA work for new expansion header
2024-01-27 Branch of uart to v1
2024-01-27 Generate step files and start on gpu for new board layout
2024-01-28 Normalize cap size
2024-02-02 Add uart to simulator
2024-02-15 Add serial terminal to simulator and uart read/write support for chars in monitor
2024-02-26 Working jump command
2024-02-26 Working loadable program support
2024-03-04 Uart and loader work
2024-03-07 Break out commands to own files and fix write command
2024-03-08 Prevent newline from overriting color attribute ram
2024-03-08 Gpu exports and housekeeping
2024-03-15 Uart eda work
2024-03-15 UART routing pass 1
2024-03-17 Checksum work, interim
2024-03-17 Add conversion board
2024-03-17 Cleanup uart
2024-03-18 Fix faulty checksum generation
2024-03-18 Check for UART recieve buffer overflow and set error flag
2024-03-18 fix(simulator): UART overflow on wrong bit in status
2024-03-19 Simulate uart baudrate
2024-03-22 Rerouting IO card
2024-03-22 Add irq flag support to simulated uart
2024-03-29 Uart latch logic
2024-03-29 Touchups before ordering
2024-04-04 Fix inverted check
2024-06-28 Uart board to v1.1...make bodges permanent :(
2024-07-12 Work on SPI with actual hardware
2024-07-12 Update simulator to match new io card via assignment
2024-07-12 Disable interupts during load
2024-08-30 Add support for USER_IRQ vector to kernel
2024-09-27 Bunch of strange SPI stuff
2024-11-21 Mostly working SPI
2025-01-06 Minor update to simulator for node 20+ compat
2025-03-03 Did stuff
2025-03-04 Add SPI
2025-03-04 Add address decode
2025-03-31 First commit with new simulator
2025-03-31 Output fixes diagnostics
2025-03-31 Fix incorrect memcontrol register description
2025-03-31 Add memcontrol display to panels
2025-04-21 Safety push
2025-04-21 Newline now scrolls screen
2025-04-21 Expose current scanline in register
2025-04-21 Derp
2025-04-28 Bunch of work around SPI and SD card reading in simulator
2025-04-28 Include SD card ops in kernel
2025-05-01 Python test to read out root directory
2025-05-02 Calcualte fat and cluster start from FAT header
2025-05-02 Start of directory parsing code
2025-05-03 Working on parsing cluster chain
2025-05-04 Can list root directory in simulator
2025-05-04 Directory enumeration now checks cluster chain in FAT
2025-05-05 Lower loglevel for raylib
2025-05-09 Minor fixes
2025-05-09 Make directory enumerator support a callback
2025-05-09 Barebones support for cd, ls and broken cat
2025-05-09 Fix off by one error
2025-05-11 Started work on userland file system functions
2025-05-12 File size was stored with wrong endian
2025-05-12 Working file handle reading
2025-05-13 Rough program loading from sd-card
2025-05-20 fix: Traces straight over GND....
2025-07-09 fix: Issue on mainboard
2026-03-07 Add all in one board
2026-03-09 WIP: Implementing new SPI and IO card
2026-03-20 Working on new SPI support
2026-03-20 WIP testing SPI
2026-03-20 Fix faulty output from test assembly
2026-03-22 Trying to debug SPI...
2026-03-22 Remove unused code
2026-03-23 Incorrect mode on SD card
2026-03-23 Remove temp logging
2026-03-24 Add disassembler to wrassilator
2026-03-25 Add support for listing file
2026-03-25 Revert back 80x60 characters display since the RPI Pico will have move vram
2026-03-26 Added bitmap mode
